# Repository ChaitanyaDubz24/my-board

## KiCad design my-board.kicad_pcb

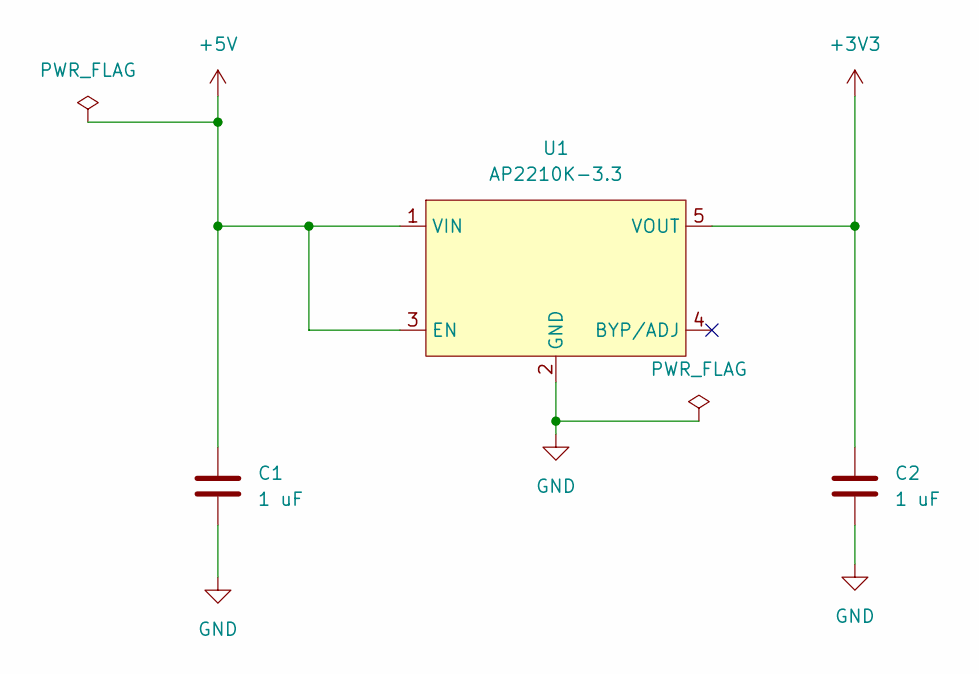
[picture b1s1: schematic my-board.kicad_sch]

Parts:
C1, C2: 1 uF; C_0603_1608Metric
U1: AP2210K-3.3; SOT-23-5_AP2210K; MPN AP2210K-3.3TRG1; LCSC C176959

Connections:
+3V3: C2.1, U1.5 (VOUT)
+5V: C1.1, U1.1 (VIN), U1.3 (EN)
GND: C1.2, C2.2, U1.2 (GND)

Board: 4 copper layers, 3 parts (0 on the bottom side), 3 nets, no tracks yet.
